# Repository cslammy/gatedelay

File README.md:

# gatedelay
I needed to delay and extend gate and trigger signals for modular synthesis and logic applications.
Uses Arduino Promini and arduino sketch. 
Allows Delay the entire signal, or just the beginning of the signal while keeping release elements intact.

For more detail please see the blog post here--there are links to earlier posts while the build was being worked out.

https://audiodiwhy.blogspot.com/2019/12/gate-delay-part-iii-works.html

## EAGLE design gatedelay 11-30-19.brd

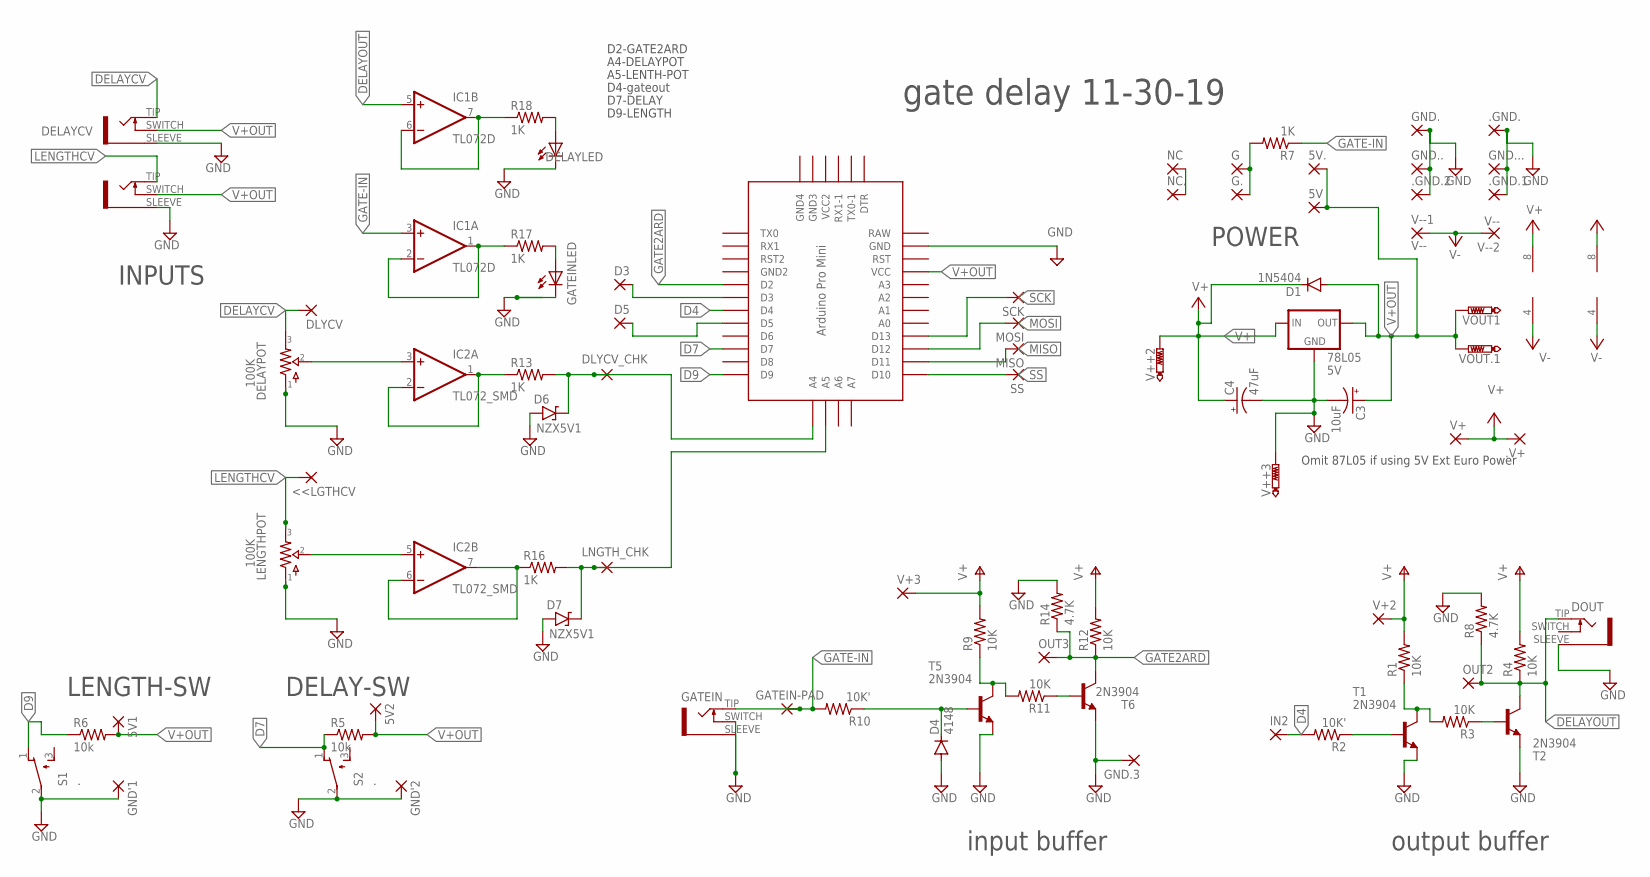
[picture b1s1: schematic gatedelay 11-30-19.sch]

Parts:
5V, 5V., .GND., .GND.1, .GND.2, .V+: 1,6/0,8
5V1, 5V2: WIREPAD2,54/0,9; 2,54/0,9
78L05: 5V; 78LXX
<<LGTHCV: 3,17/1,3
C3: 10uF; E2,5-6
C4: 47uF; E2,5-7
D1: 1N5404; DO35-10
D3, D5: WIREPAD2,15/1,0; 2,15/1,0
D4: 4148; DO35-7
D6, D7: NZX5V1; DO41-2
DELAYCV: 35RAPC2AV; 35RAPCVAV
DELAYLED: LED3MM
DELAYPOT: 100K; 9MM_VERT
DLYCV: WIREPAD1,6/0,9; 1,6/0,9
DLYCV_CHK: 3,17/1,3
DOUT: 35RAPC2AV; 35RAPCVAV
G, G.: 1,6/0,8
GATEIN: 35RAPC2AV; 35RAPCVAV
GATEIN-PAD: WIREPAD1,6/0,9; 1,6/0,9
GATEINLED: LED3MM
GND'1, GND'2: WIREPAD2,54/0,9; 2,54/0,9
GND., GND.., GND...: 1,6/0,8
GND.3: WIREPAD1,6/0,9; 1,6/0,9
IC1: TL072D; SO08
IC2: TL072_SMD; SO08
IN2: WIREPAD1,6/0,9; 1,6/0,9
LENGTHCV: 35RAPC2AV; 35RAPCVAV
LENGTHPOT: 100K; 9MM_VERT
LNGTH_CHK: 3,17/1,3
MISO: WIREPAD1,6/0,9; 1,6/0,9
MOSI: WIREPAD1,6/0,9; 1,6/0,9
NC, NC.: 1,6/0,8
OUT2, OUT3: WIREPAD1,6/0,9; 1,6/0,9
R1, R3, R4, R9, R11, R12: 10K; 0204/5
R2, R10: 10K'; 0204/5
R5: 10k; 0207/10
R6: 10k; 0204/5
R7: 1K; 0207/7
R8, R14: 4.7K; 0204/5
R13, R16, R17: 1K; 0204/7
R18: 1K; 0207/15
S1, S2: .; ALCOSWTT11
SCK: WIREPAD1,6/0,9; 1,6/0,9
SS: WIREPAD1,6/0,9; 1,6/0,9
T1, T2, T5, T6: 2N3904; TO92
U$1: PRO-MINI
V+: 1,6/0,8
V+2, V+3: WIREPAD1,6/0,9; 1,6/0,9
V++2, V++3: PTR1PAD1-13Y; P1-13Y
V--1, V--2: V--; 1,6/0,8
VOUT1, VOUT.1: PTR1PAD1-13Y; P1-13Y

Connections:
D4: IN2.1, R2.2, U$1.D4
D7: R5.1, S2.1 (O), U$1.D7
D9: R6.1, S1.1 (O), U$1.D9
DELAYCV: DELAYCV.TIP (2), DELAYPOT.3, DLYCV.1
DELAYOUT: DOUT.TIP (2), IC1.5 (+IN), OUT2.1, R4.1, R8.1, T2.1 (C)
GATE2ARD: OUT3.1, R12.1, R14.1, T6.1 (C), U$1.D2
GATE-IN: GATEIN.TIP (2), GATEIN-PAD.1, IC1.3 (+IN), R7.1, R10.2
GND: 78L05.GND, .GND..1, .GND.1.1, .GND.2.1, C3.-, C4.-, D4.A, D6.A, D7.A, DELAYCV.SLEEVE (1), DELAYLED.K (C), DELAYPOT.1, DOUT.SLEEVE (1), GATEIN.SLEEVE (1), GATEIN.SWITCH (3), GATEINLED.K (C), GND'1.1, GND'2.1, GND..1, GND.3.1, GND...1, GND....1, LENGTHCV.SLEEVE (1), LENGTHPOT.1, R8.2, R14.2, S1.2, S2.2, T1.3 (E), T2.3 (E), T5.3 (E), T6.3 (E), U$1.GND, V++3.TP
LENGTHCV: <<LGTHCV.1, LENGTHCV.TIP (2), LENGTHPOT.3
MISO: MISO.1, U$1.D11
MOSI: MOSI.1, U$1.D12
unnamed: D5.1, U$1.D5
unnamed: R2.1, T1.2 (B)
unnamed: R1.1, R3.2, T1.1 (C)
unnamed: R3.1, T2.2 (B)
unnamed: G.1, G..1, R7.2
unnamed: D3.1, U$1.D3
unnamed: NC.1, NC..1
unnamed: D4.C, R10.1, T5.2 (B)
unnamed: R9.1, R11.2, T5.1 (C)
unnamed: R11.1, T6.2 (B)
unnamed: D6.C, DLYCV_CHK.1, R13.2, U$1.A4
unnamed: DELAYPOT.2, IC2.3 (+IN)
unnamed: IC2.1 (OUT), IC2.2 (-IN), R13.1
unnamed: IC2.5 (+IN), LENGTHPOT.2
unnamed: IC2.6 (-IN), IC2.7 (OUT), R16.1
unnamed: D7.C, LNGTH_CHK.1, R16.2, U$1.A5
unnamed: GATEINLED.A, R17.2
unnamed: IC1.1 (OUT), IC1.2 (-IN), R17.1
unnamed: IC1.6 (-IN), IC1.7 (OUT), R18.1
unnamed: DELAYLED.A, R18.2
RAW: U$1.RAW
SCK: SCK.1, U$1.D13
SS: SS.1, U$1.D10
V+: 78L05.IN, .V+.1, C4.+, D1.C, IC1.8 (V+), IC2.8 (V+), R1.2, R4.2, R9.2, R12.2, V+.1, V+2.1, V+3.1, V++2.TP
V+OUT: 5V.1, 5V1.1, 5V2.1, 5V..1, 78L05.OUT, C3.+, D1.A, DELAYCV.SWITCH (3), LENGTHCV.SWITCH (3), R5.2, R6.2, U$1.VCC, VOUT1.TP, VOUT.1.TP
V-: IC1.4 (V-), IC2.4 (V-), V--1.1, V--2.1

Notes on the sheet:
POWER
DELAY-SW
LENGTH-SW
gate delay 11-30-19
output buffer
input buffer
D7-DELAY
D9-LENGTH
D4-gateout
A5-LENTH-POT
A4-DELAYPOT
D2-GATE2ARD
INPUTS
Omit 87L05 if using 5V Ext Euro Power

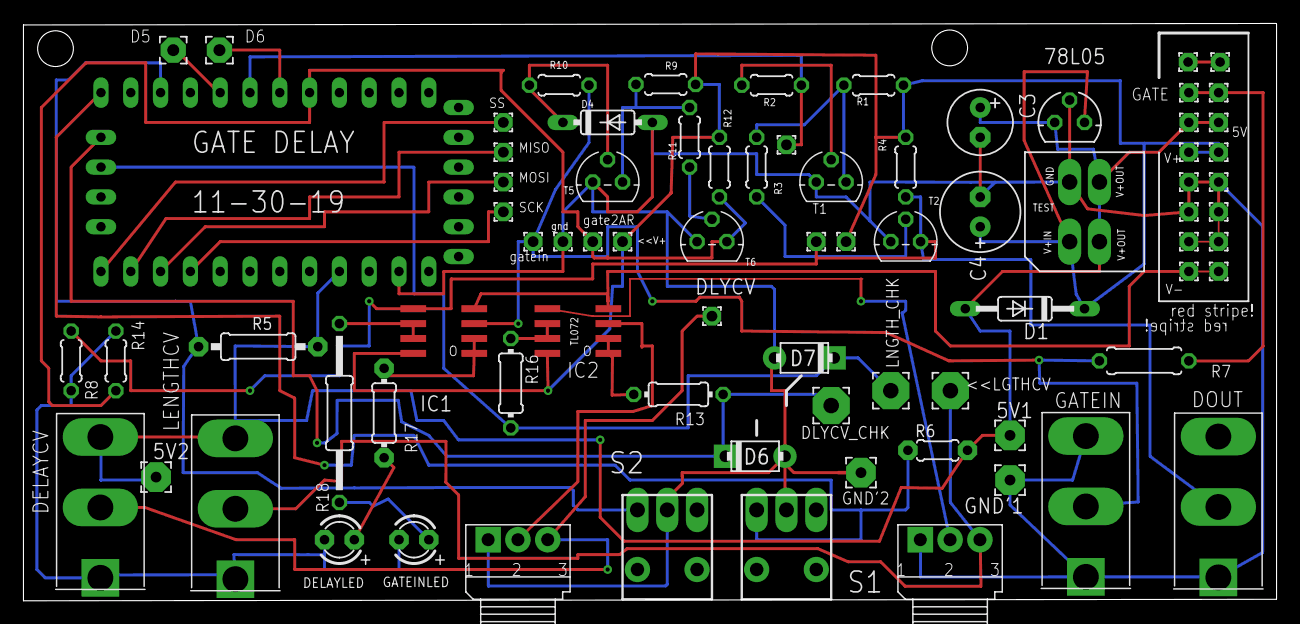
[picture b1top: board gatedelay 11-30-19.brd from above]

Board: 2 copper layers, 106.8 x 49.2 mm, 82 parts (0 on the bottom side), 36 nets.

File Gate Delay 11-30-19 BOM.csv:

Part,Value,Device,Package,Description,POPULARITY,SPICEPREFIX,TP_SIGNAL_NAME,Column1
78L05,5V,78LXX,78LXX,VOLTAGE REGULATOR,,,,
C3,10uF,CPOL-USE2.5-6,"E2,5-6","POLARIZED CAPACITOR, American symbol",,,,
C4,47uF,CPOL-USE2.5-7,"E2,5-7","POLARIZED CAPACITOR, American symbol",,,,
D1,1N5404,1N4148DO35-10,DO35-10,DIODE,21,,,
D3,,"WIREPAD2,15/1,0","2,15/1,0",Wire PAD connect wire on PCB,2,,,
D4,4148,1N4148DO35-7,DO35-7,DIODE,58,,,
D5,,"WIREPAD2,15/1,0","2,15/1,0",Wire PAD connect wire on PCB,2,,,
D6,NZX5V1,ZENER.2,DO41-2,,,,,
D7,NZX5V1,ZENER.2,DO41-2,,,,,
DELAYCV,,35RAPC2AV,35RAPCVAV,Switchcraft 35RAPC2AV jack,,,,
DELAYLED,,LED3MM,LED3MM,LED,,,,
DELAYPOT,100K,POTS9MM_VERT,9MM_VERT,,,,,
DLYCV_CHK,,"3,17/1,3","3,17/1,3",THROUGH-HOLE PAD,3,,,
DOUT,,35RAPC2AV,35RAPCVAV,Switchcraft 35RAPC2AV jack,,,,
GATEIN,,35RAPC2AV,35RAPCVAV,Switchcraft 35RAPC2AV jack,,,,
GATEINLED,,LED3MM,LED3MM,LED,,,,
IC1,TL072D,TL072D,SO08,OP AMP,,,,
IC2,TL072_SMD,TL072_SMD,SO08,Generic Dual Op Amp,,,,
LENGTHCV,,35RAPC2AV,35RAPCVAV,Switchcraft 35RAPC2AV jack,,,,
LENGTHPOT,100K,POTS9MM_VERT,9MM_VERT,,,,,
R1,10K,R-US_0204/5,0204/5,"RESISTOR, American symbol",18,R,,
R2,10K',R-US_0204/5,0204/5,"RESISTOR, American symbol",18,R,,
R3,10K,R-US_0204/5,0204/5,"RESISTOR, American symbol",18,R,,
R4,10K,R-US_0204/5,0204/5,"RESISTOR, American symbol",18,R,,
R5,10k,R-US_0207/10,0207/10,"RESISTOR, American symbol",,,,
R6,10k,R-US_0204/5,0204/5,"RESISTOR, American symbol",,,,
R7,1K,R-US_0207/7,0207/7,"RESISTOR, American symbol",,,,
R8,4.7K,R-US_0204/5,0204/5,"RESISTOR, American symbol",18,R,,
R9,10K,R-US_0204/5,0204/5,"RESISTOR, American symbol",18,R,,
R10,10K',R-US_0204/5,0204/5,"RESISTOR, American symbol",18,R,,
R11,10K,R-US_0204/5,0204/5,"RESISTOR, American symbol",18,R,,
R12,10K,R-US_0204/5,0204/5,"RESISTOR, American symbol",18,R,,
R13,1K,R-US_0204/7,0204/7,"RESISTOR, American symbol",,,,
R14,4.7K,R-US_0204/5,0204/5,"RESISTOR, American symbol",18,R,,
R16,1K,R-US_0204/7,0204/7,"RESISTOR, American symbol",,,,
R17,1K,R-US_0204/7,0204/7,"RESISTOR, American symbol",,,,
R18,1K,R-US_0207/15,0207/15,"RESISTOR, American symbol",0,R,,
S1,.,ALCOSWTT11,ALCOSWTT11,TINY SWITCH ON - MOM,,,,
S2,.,ALCOSWTT11,ALCOSWTT11,TINY SWITCH ON - MOM,,,,
T1,2N3904,2N3904,TO92,NPN TRANSISTOR,27,,,
T2,2N3904,2N3904,TO92,NPN TRANSISTOR,27,,,
T5,2N3904,2N3904,TO92,NPN TRANSISTOR,27,,,
T6,2N3904,2N3904,TO92,NPN TRANSISTOR,27,,,
U$1,PRO-MINI,PRO-MINI,PRO-MINI,Arduion Pro Mini Clone V1.0,,,,

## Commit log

2020-12-31 Initial upload
2022-11-22 BOM as requested
2022-11-22 Update README.md
    Include link to blog post for the project
